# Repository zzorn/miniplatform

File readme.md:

Generic electronic pcb for arduino pro mini and various sensors and outputs.

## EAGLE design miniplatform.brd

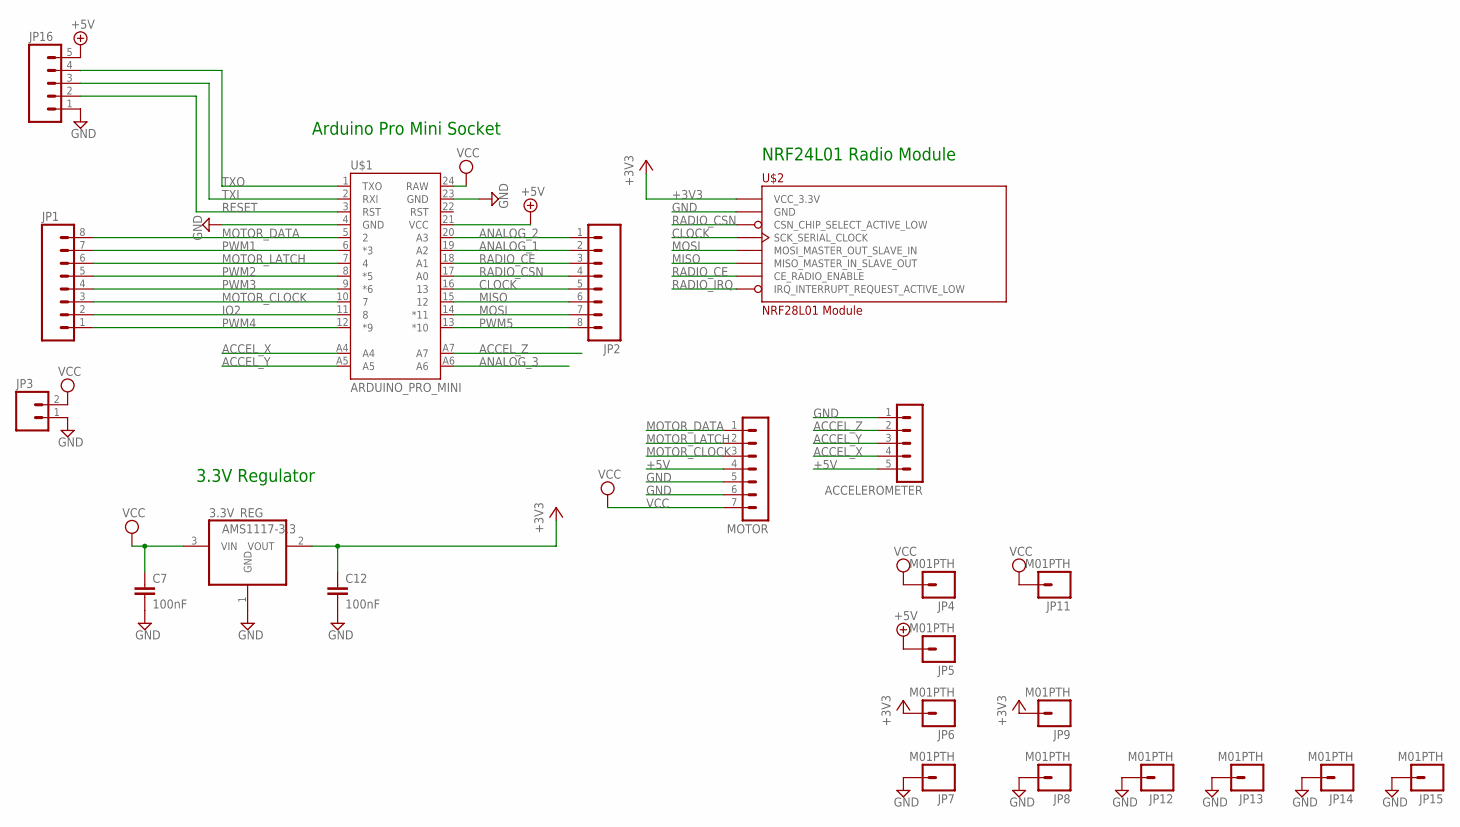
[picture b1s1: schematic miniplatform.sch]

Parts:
3.3V_REG: AMS1117-3.3; SOT223
ACCELEROMETER: MA05-1
C7, C12: 100nF; C0805K
JP1, JP2: M081X08; 1X08
JP3: M02LOCK_LONGPADS; 1X02_LOCK_LONGPADS
JP4, JP5, JP6, JP7, JP8, JP9, JP11, JP12, JP13, JP14, JP15: M01PTH; 1X01
JP16: M05PTH; 1X05
MOTOR: MA07-1
U$1: ARDUINO_PRO_MINI
U$2: NRF28L01 Module; NRF24L01_MODULE

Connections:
+3V3: 3.3V_REG.2 (VOUT), C12.1, JP6.1, JP9.1, U$2.P$2 (VCC_3.3V)
+5V: 3.3V_REG.3 (VIN), ACCELEROMETER.5, C7.1, JP5.1, JP16.5, MOTOR.4, U$1.21 (VCC)
+12V: U$1.24 (RAW)
ACCEL_X: ACCELEROMETER.4, U$1.A4
ACCEL_Y: ACCELEROMETER.3, U$1.A5
ACCEL_Z: ACCELEROMETER.2, U$1.A7
ANALOG_1: JP2.2, U$1.19 (A2)
ANALOG_2: JP2.1, U$1.20 (A3)
ANALOG_3: U$1.A6
CLOCK: JP2.5, U$1.16 (13), U$2.P$5 (SCK_SERIAL_CLOCK)
GND: 3.3V_REG.1 (GND), ACCELEROMETER.1, C7.2, C12.2, JP3.1, JP7.1, JP8.1, JP12.1, JP13.1, JP14.1, JP15.1, JP16.1, MOTOR.5, MOTOR.6, U$1.4 (GND), U$1.23 (GND), U$2.P$1 (GND)
IO2: JP1.2, U$1.11 (8)
MISO: JP2.6, U$1.15 (12), U$2.P$7 (MISO_MASTER_IN_SLAVE_OUT)
MOSI: JP2.7, U$1.14 (*11), U$2.P$6 (MOSI_MASTER_OUT_SLAVE_IN)
MOTOR_CLOCK: JP1.3, MOTOR.3, U$1.10 (7)
MOTOR_DATA: JP1.8, MOTOR.1, U$1.5 (2)
MOTOR_LATCH: JP1.6, MOTOR.2, U$1.7 (4)
PWM1: JP1.7, U$1.6 (*3)
PWM2: JP1.5, U$1.8 (*5)
PWM3: JP1.4, U$1.9 (*6)
PWM4: JP1.1, U$1.12 (*9)
PWM5: JP2.8, U$1.13 (*10)
RADIO_CE: JP2.3, U$1.18 (A1), U$2.P$3 (CE_RADIO_ENABLE)
RADIO_CSN: JP2.4, U$1.17 (A0), U$2.P$4 (CSN_CHIP_SELECT_ACTIVE_LOW)
RADIO_IRQ: U$2.P$8 (IRQ_INTERRUPT_REQUEST_ACTIVE_LOW)
RESET: JP16.2, U$1.3 (RST)
TXI: JP16.3, U$1.2 (RXI)
TXO: JP16.4, U$1.1 (TXO)
VCC: JP3.2, JP4.1, JP11.1, MOTOR.7

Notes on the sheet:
Arduino Pro Mini Socket
3.3V Regulator
NRF24L01 Radio Module

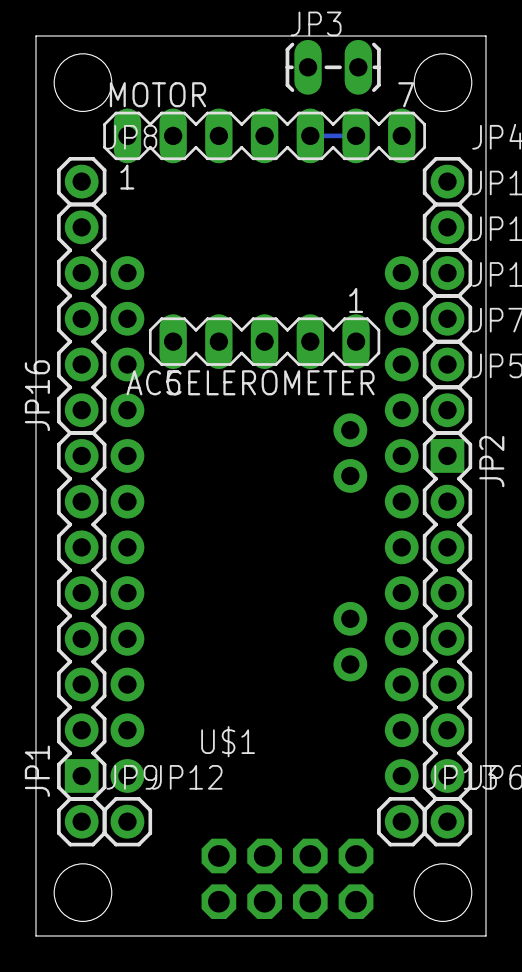
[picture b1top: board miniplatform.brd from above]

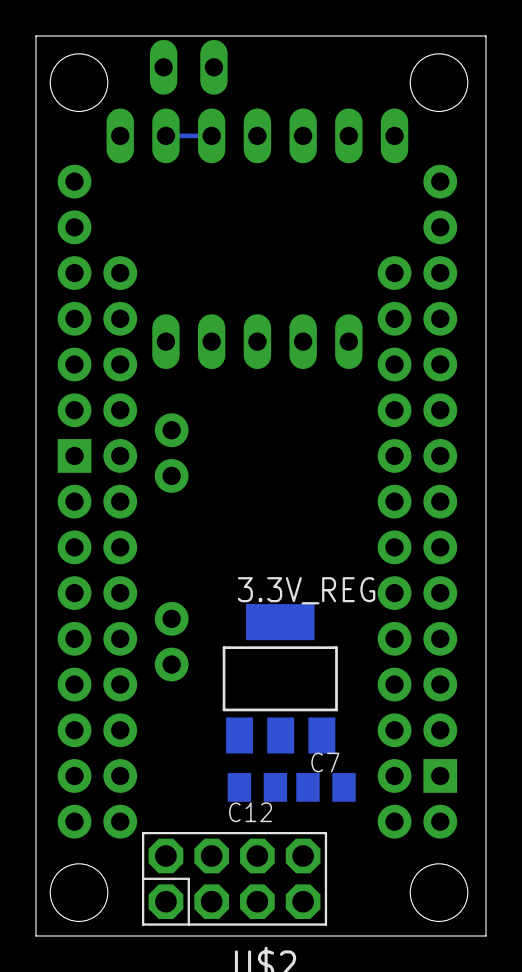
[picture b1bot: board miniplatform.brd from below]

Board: 2 copper layers, 25.0 x 50.0 mm, 22 parts (4 on the bottom side), 26 nets.

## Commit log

2015-04-26 Added readme
2015-04-26 Some work on pcb.
2015-04-26 Layout work.
2015-04-27 Tuned layout.

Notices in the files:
parts and their libraries:
SparkFun-Boards-with-arduino-pro-mini-wi: Licensing: Creative Commons ShareAlike 4.0 International - https://creativecommons.org/licenses/by-sa/4.0
SparkFun: Licensing: CC v3.0 Share-Alike You are welcome to use this library for commercial purposes.
